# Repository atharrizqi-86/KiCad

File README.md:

MBKM BRIN 2026

**PCB Design & Development**  
Made with KiCad 10.0

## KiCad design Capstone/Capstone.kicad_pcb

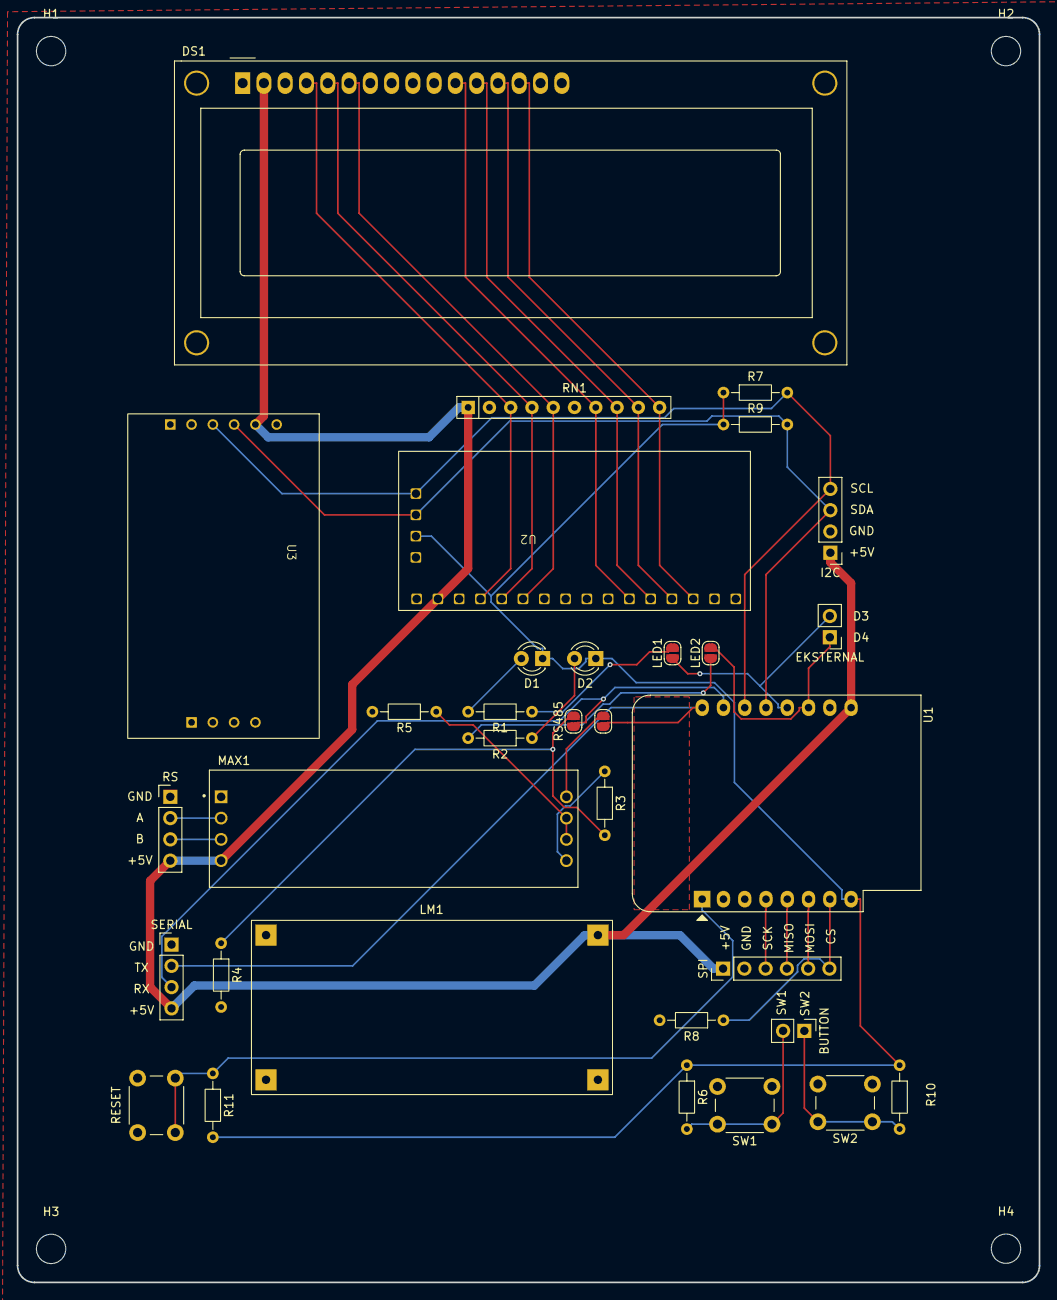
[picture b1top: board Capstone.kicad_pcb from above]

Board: 2 copper layers, 122.0 x 151.0 mm, 37 parts (0 on the bottom side), 33 nets.

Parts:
BUTTON: PinHeader_1x02_P2.54mm_Vertical
D1, D2: LED; LED_D3.0mm
DS1: WC1602A
EKSTERNAL: EKSTERNAL; PinHeader_1x02_P2.54mm_Vertical
H1, H2, H3, H4: MountingHole; MountingHole_3.5mm
I2C: I2C; PinHeader_1x04_P2.54mm_Vertical
JP4: SolderJumper_2_Open; SolderJumper-2_P1.3mm_Open_RoundedPad1.0x1.5mm
LED1, LED2: SolderJumper_2_Open; SolderJumper-2_P1.3mm_Open_RoundedPad1.0x1.5mm
LM1: LM2596_Module; LM2596-DC-DC
MAX1: MAX485_MODULE; MODULE_MAX485_MODULE_5V_LOGIC_TLL_TO_RS-485_CONVERTER
R1, R2: 1K; R_Axial_DIN0204_L3.6mm_D1.6mm_P7.62mm_Horizontal
R3: 1k; R_Axial_DIN0204_L3.6mm_D1.6mm_P7.62mm_Horizontal
R4: 2k; R_Axial_DIN0204_L3.6mm_D1.6mm_P7.62mm_Horizontal
R5: 10k; R_Axial_DIN0204_L3.6mm_D1.6mm_P7.62mm_Horizontal
R6, R8, R10, R11: 10K; R_Axial_DIN0204_L3.6mm_D1.6mm_P7.62mm_Horizontal
R7, R9: 4.7K; R_Axial_DIN0204_L3.6mm_D1.6mm_P7.62mm_Horizontal
RESET: SW_Push; SW_PUSH_6mm
RN1: R_Network09; R_Array_SIP10
RS: RS485; PinHeader_1x04_P2.54mm_Vertical
RS485: SolderJumper_2_Open; SolderJumper-2_P1.3mm_Open_RoundedPad1.0x1.5mm
SERIAL: Serial; PinHeader_1x04_P2.54mm_Vertical
SPI: SPI; PinHeader_1x06_P2.54mm_Vertical
SW1, SW2: SW_Push; SW_PUSH_6mm
U1: WEMOS_D1_mini; WEMOS_D1_mini_light
U2: PCF8574AP; PCF8574
U3: DS3231M; MODULE_DS3231

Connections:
+3.3V: D1.1 (K), D2.1 (K), R6.1, R7.1, R9.1, R10.1, R11.2, U1.8 (3V3), U2.16 (VDD)
+5V: DS1.2 (VDD), I2C.1, LM1.4 (OUT+), MAX1.4 (VCC), RN1.1 (common), RS.4, SERIAL.4, SPI.1, U1.9 (5V), U2.1, U3.5 (GND)
/CS: R8.1, SPI.6, U1.7 (CS/D8)
/D3: EKSTERNAL.2, LED1.1 (A), U1.12 (D3)
/D4: EKSTERNAL.1, LED2.2 (B), U1.11 (D4)
/MISO: SPI.4, U1.5 (MISO/D6)
/MOSI: SPI.5, U1.6 (MOSI/D7)
/RST: R11.1, RESET.1, U1.1 (~RST)
/SCK: SPI.3, U1.4 (SCK/D5)
/SCL: I2C.4, R7.2, U1.14 (SCL/D1), U2.14 (SCL), U3.3 (~INT/SQW)
/SDA: I2C.3, R9.2, U1.13 (SDA/D2), U2.15 (SDA), U3.4 (~RST)
GND: DS1.1 (VSS), I2C.2, LM1.3 (OUT-), MAX1.1 (GND), R4.2, R5.2, R8.2, RESET.2, RS.1, SERIAL.1, SPI.2, SW1.2, SW2.2, U1.3 (D0), U1.10 (GND), U2.8 (GND), U3.5 (GND), U3.6 (GND)
unnamed: BUTTON.1, R10.2, SW2.1
unnamed: BUTTON.2, R6.2, SW1.1
unnamed: D1.2 (A), R1.2
unnamed: D2.2 (A), R2.1
unnamed: DS1.11 (D4), RN1.7 (R6), U2.9 (P4)
unnamed: DS1.12 (D5), RN1.8 (R7), U2.10 (P5)
unnamed: DS1.13 (D6), RN1.9 (R8), U2.11 (P6)
unnamed: DS1.14 (D7), RN1.10 (R9), U2.12 (P7)
unnamed: DS1.6 (E), RN1.5 (R4), U2.6 (P2)
unnamed: DS1.4 (RS), RN1.3 (R2), U2.4 (P0)
unnamed: DS1.5 (R/W), RN1.4 (R3), U2.5 (P1)
unnamed: RS485.1 (A), SERIAL.3, U1.15 (RX)
unnamed: R3.2, R4.1, RS485.2 (B)
unnamed: LED1.2 (B), R1.1
unnamed: LED2.1 (A), R2.2
unnamed: JP4.1 (A), SERIAL.2, U1.16 (TX)
unnamed: JP4.2 (B), MAX1.8 (DI)
unnamed: MAX1.2 (A), RS.2
unnamed: MAX1.3 (B), RS.3
unnamed: MAX1.6 (RE), MAX1.7 (DE), R5.1
unnamed: MAX1.5 (RO), R3.1

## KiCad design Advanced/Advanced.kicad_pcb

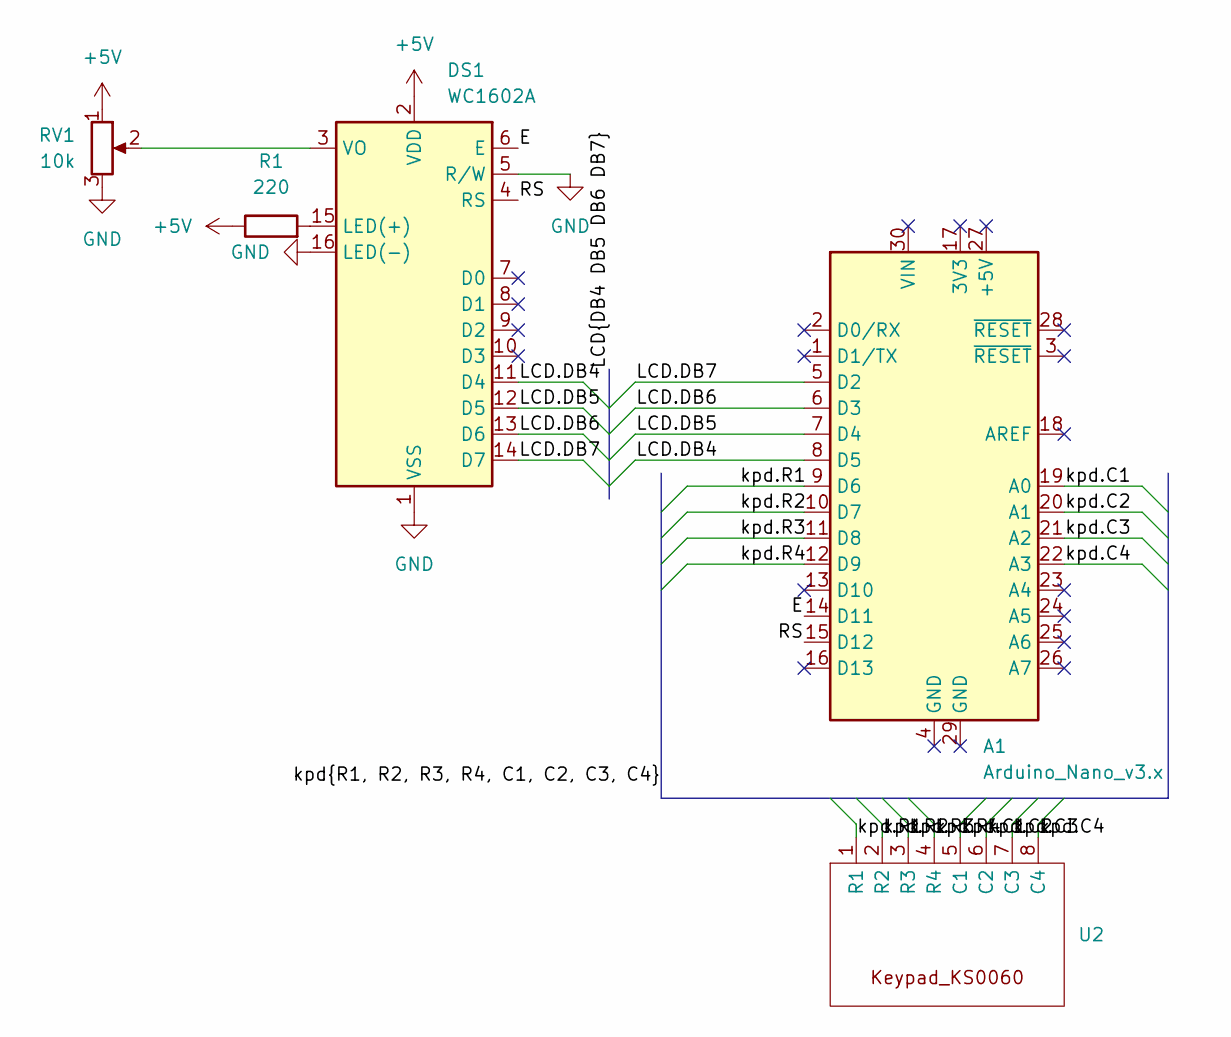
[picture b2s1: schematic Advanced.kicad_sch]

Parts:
A1: Arduino_Nano_v3.x; Arduino_Nano
DS1: WC1602A
R1: 220; R_Axial_DIN0204_L3.6mm_D1.6mm_P5.08mm_Horizontal
RV1: 10k; Potentiometer_Bourns_3266W_Vertical
U2: PinSocket_1x08_P2.54mm_Horizontal

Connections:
+5V: DS1.2 (VDD), R1.1, RV1.1
/E: A1.14 (D11), DS1.6 (E)
/LCD.DB4: A1.8 (D5), DS1.11 (D4)
/LCD.DB5: A1.7 (D4), DS1.12 (D5)
/LCD.DB6: A1.6 (D3), DS1.13 (D6)
/LCD.DB7: A1.5 (D2), DS1.14 (D7)
/RS: A1.15 (D12), DS1.4 (RS)
/kpd.C1: A1.19 (A0), U2.5 (C1)
/kpd.C2: A1.20 (A1), U2.6 (C2)
/kpd.C3: A1.21 (A2), U2.7 (C3)
/kpd.C4: A1.22 (A3), U2.8 (C4)
/kpd.R1: A1.9 (D6), U2.1 (R1)
/kpd.R2: A1.10 (D7), U2.2 (R2)
/kpd.R3: A1.11 (D8), U2.3 (R3)
/kpd.R4: A1.12 (D9), U2.4 (R4)
GND: DS1.1 (VSS), DS1.5 (R/W), DS1.16 (LED(-)), RV1.3
unnamed: DS1.15 (LED(+)), R1.2
unnamed: DS1.3 (VO), RV1.2

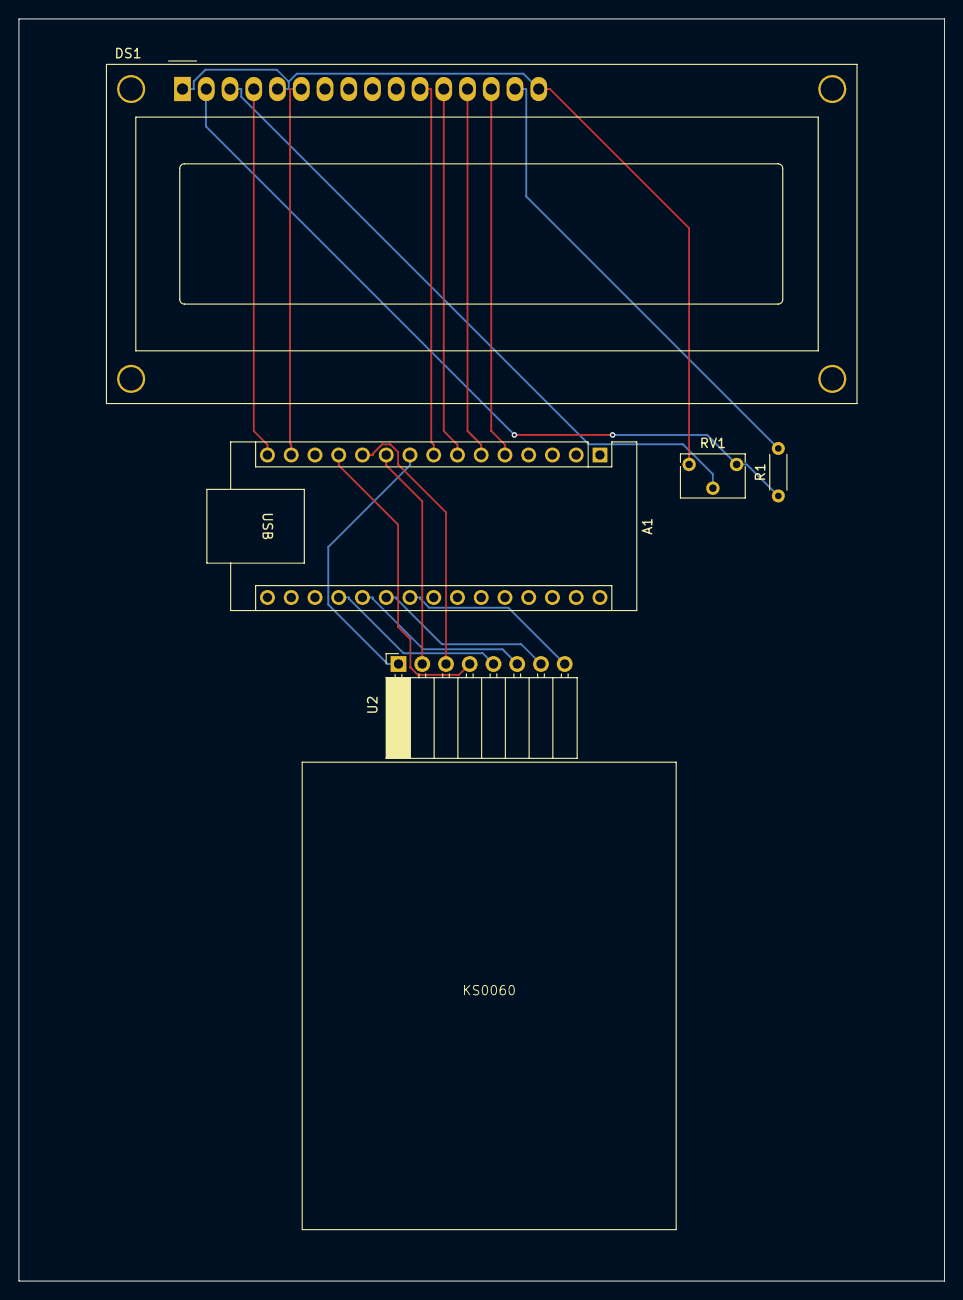
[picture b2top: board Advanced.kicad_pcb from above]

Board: 2 copper layers, 99.0 x 135.0 mm, 5 parts (0 on the bottom side), 18 nets.

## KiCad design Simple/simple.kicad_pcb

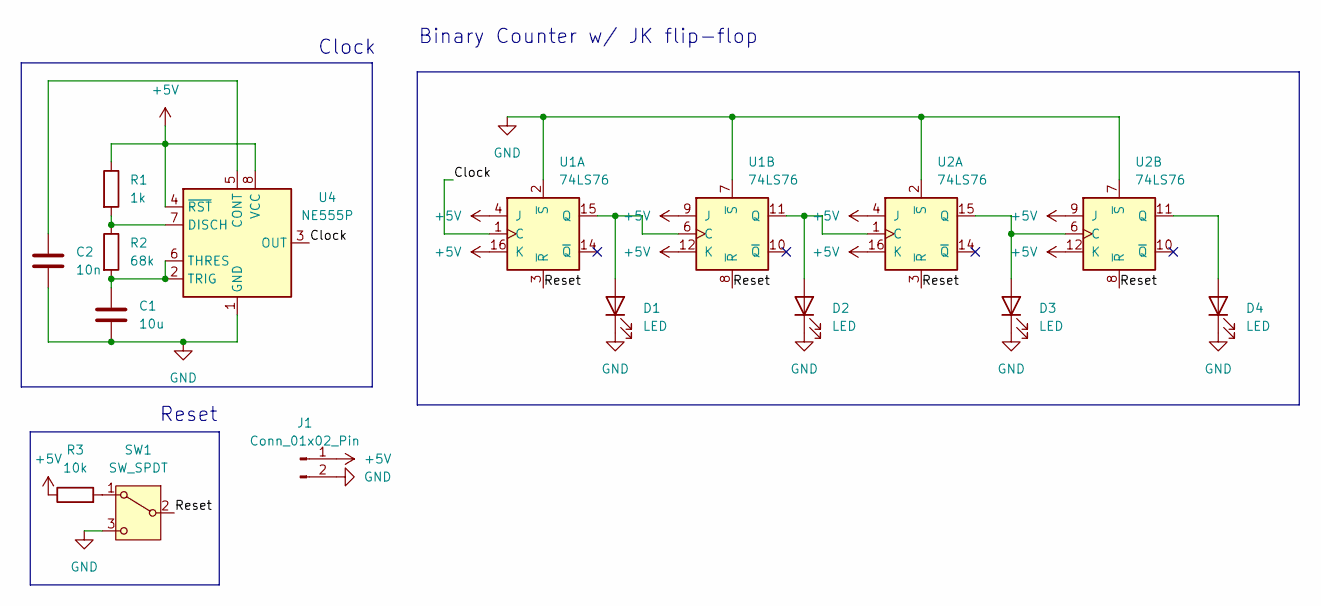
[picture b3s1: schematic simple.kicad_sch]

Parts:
C1: 10u; CP_Radial_D5.0mm_P2.50mm
C2: 10n; C_Disc_D3.0mm_W1.6mm_P2.50mm
D1, D2, D3, D4: LED; LED_D3.0mm
J1: Conn_01x02_Pin; Molex_KK-254_AE-6410-02A_1x02_P2.54mm_Vertical
R1: 1k; R_Axial_DIN0204_L3.6mm_D1.6mm_P5.08mm_Horizontal
R2: 68k; R_Axial_DIN0204_L3.6mm_D1.6mm_P5.08mm_Horizontal
R3: 10k; R_Axial_DIN0204_L3.6mm_D1.6mm_P5.08mm_Horizontal
SW1: SW_SPDT; SW_Slide-03_Wuerth-WS-SLTV_10x2.5x6.4_P2.54mm
U1, U2: 74LS76; DIP-16_W7.62mm
U4: NE555P; DIP-8_W7.62mm

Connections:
+5V: J1.1, R1.1, R3.1, U1.4 (J), U1.9 (J), U1.12 (K), U1.16 (K), U2.4 (J), U2.9 (J), U2.12 (K), U2.16 (K), U4.4 (~RST), U4.8 (VCC)
/Clock: U1.1 (C), U4.3 (OUT)
/Reset: SW1.2 (B), U1.3 (~R), U1.8 (~R), U2.3 (~R), U2.8 (~R)
GND: C1.2, C2.2, D1.1 (K), D2.1 (K), D3.1 (K), D4.1 (K), J1.2, SW1.3 (C), U1.2 (~S), U1.7 (~S), U2.2 (~S), U2.7 (~S), U4.1 (GND)
unnamed: D1.2 (A), U1.6 (C), U1.15 (Q)
unnamed: D2.2 (A), U1.11 (Q), U2.1 (C)
unnamed: D3.2 (A), U2.6 (C), U2.15 (Q)
unnamed: D4.2 (A), U2.11 (Q)
unnamed: R3.2, SW1.1 (A)
unnamed: C2.1, U4.5 (CONT)
unnamed: R1.2, R2.1, U4.7 (DISCH)
unnamed: C1.1, R2.2, U4.2 (TRIG), U4.6 (THRES)

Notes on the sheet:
Binary Counter w/ JK flip-flop
Reset
Clock

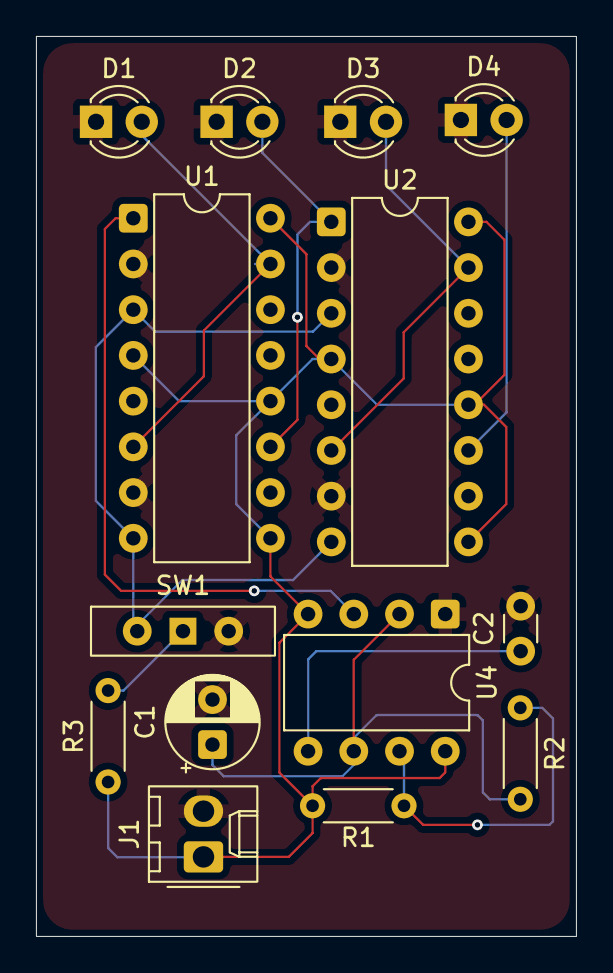
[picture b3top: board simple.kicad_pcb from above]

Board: 4 copper layers, 30.0 x 50.0 mm, 14 parts (0 on the bottom side), 12 nets.

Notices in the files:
Simple/simple.kicad_pcb:
COPYRIGHT © ALL RIGHTS RESERVED
